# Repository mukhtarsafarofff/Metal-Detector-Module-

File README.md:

(ENG) We can find a metal detector at airports, theaters and various other public places. They are used for the safety of people to detect anyone carrying a metal.  In this project I am  going to design a simple metal detector circuit. There are so many metal detector designs but most of them are complex in design so here I am going to design a simple metal detector circuit using 555 Timer IC. In this circuit if the inductance value changes the value of reactance or impedance changes. The 555 IC timer here acts as a square wave generator and it generate pulses with frequencies audible to human. The capacitor between pin2 and pin1 should not be changed as it is need to generate audible frequencies. In this circuit you can see RLC circuit. RLC circuit is the metal detection part here. When a metal piece is brought near the coil, the metal piece acts as a core for the air cored inductor. By this metal acting as a core, the inductance of the coil changes or increases considerably. With this sudden increase in inductance of coil the overall reactance or impedance of the RLC circuit changes by a considerable amount when compared without the metal piece. At first when there is no metal piece the signal fed to speaker causes some audible sound. Now with the reactance change around the RLC circuit the signal sent to speaker will no longer be the same as before, because of this the sound produced by the speaker will be of different to the first one.  So whenever a metal is brought near the coil, the impedance of RLC changes making the signal to change resulting in variation to sound generated in speaker.  Enamel should be removed at the tips of coil for soldering connections. With different gauge we will have different RLC impedance, so one should experiment with resistance in RLC circuit for sensitive metal detection.

(DEU) Wir können Metalldetektoren an Flughäfen, in Theatern und an verschiedenen anderen öffentlichen Orten finden. Sie werden zur Sicherheit der Menschen eingesetzt, um Personen mit Metallgegenständen zu erkennen. In diesem Projekt werde ich einen einfachen Metalldetektorschaltkreis entwerfen. . Es gibt viele Metalldetektordesigns, aber die meisten sind komplex im Aufbau, daher werde ich hier einen einfachen Metalldetektorschaltkreis unter Verwendung eines 555-Timer-ICs entwerfen. In diesem Schaltkreis ändert sich der Wert der Reaktanz oder Impedanz, wenn sich der Induktivitätswert ändert.  Der 555-Timer-IC fungiert hier als Rechteckwellengenerator und erzeugt Impulse mit für den Menschen hörbaren Frequenzen. Der Kondensator zwischen Pin 2 und Pin 1 sollte nicht geändert werden, da er benötigt wird, um hörbare Frequenzen zu erzeugen.  In diesem Schaltkreis können Sie einen RLC-Schaltkreis sehen. Der RLC-Schaltkreis ist hier der Metalldetektionsteil. Wenn ein Metallstück in die Nähe der Spule gebracht wird, fungiert das Metallstück als Kern für die luftgekoppelte Induktivität. Durch dieses Metall, das als Kern fungiert, ändert oder erhöht sich die Induktivität der Spule erheblich.  Durch diese plötzliche Erhöhung der Induktivität der Spule ändert sich die gesamte Reaktanz oder Impedanz des RLC-Schaltkreises erheblich im Vergleich zu einem Zustand ohne Metallstück. Zunächst verursacht das Signal, das zum Lautsprecher geleitet wird, ein hörbares Geräusch, wenn kein Metallstück vorhanden ist.  Mit der Reaktanzänderung im RLC-Schaltkreis wird das Signal, das zum Lautsprecher gesendet wird, nicht mehr dasselbe sein wie zuvor, wodurch das vom Lautsprecher erzeugte Geräusch anders ist als das erste. Immer wenn ein Metall in die Nähe der Spule gebracht wird, ändert sich die Impedanz des RLC-Schaltkreises, wodurch sich das Signal ändert und somit das im Lautsprecher erzeugte Geräusch variiert.  Der Emaillelack sollte an den Enden der Spule für Lötverbindungen entfernt werden. Mit unterschiedlichem Drahtdurchmesser haben wir unterschiedliche RLC-Impedanzen, daher sollte man mit dem Widerstand im RLC-Schaltkreis experimentieren, um eine empfindliche Metalldetektion zu erreichen.

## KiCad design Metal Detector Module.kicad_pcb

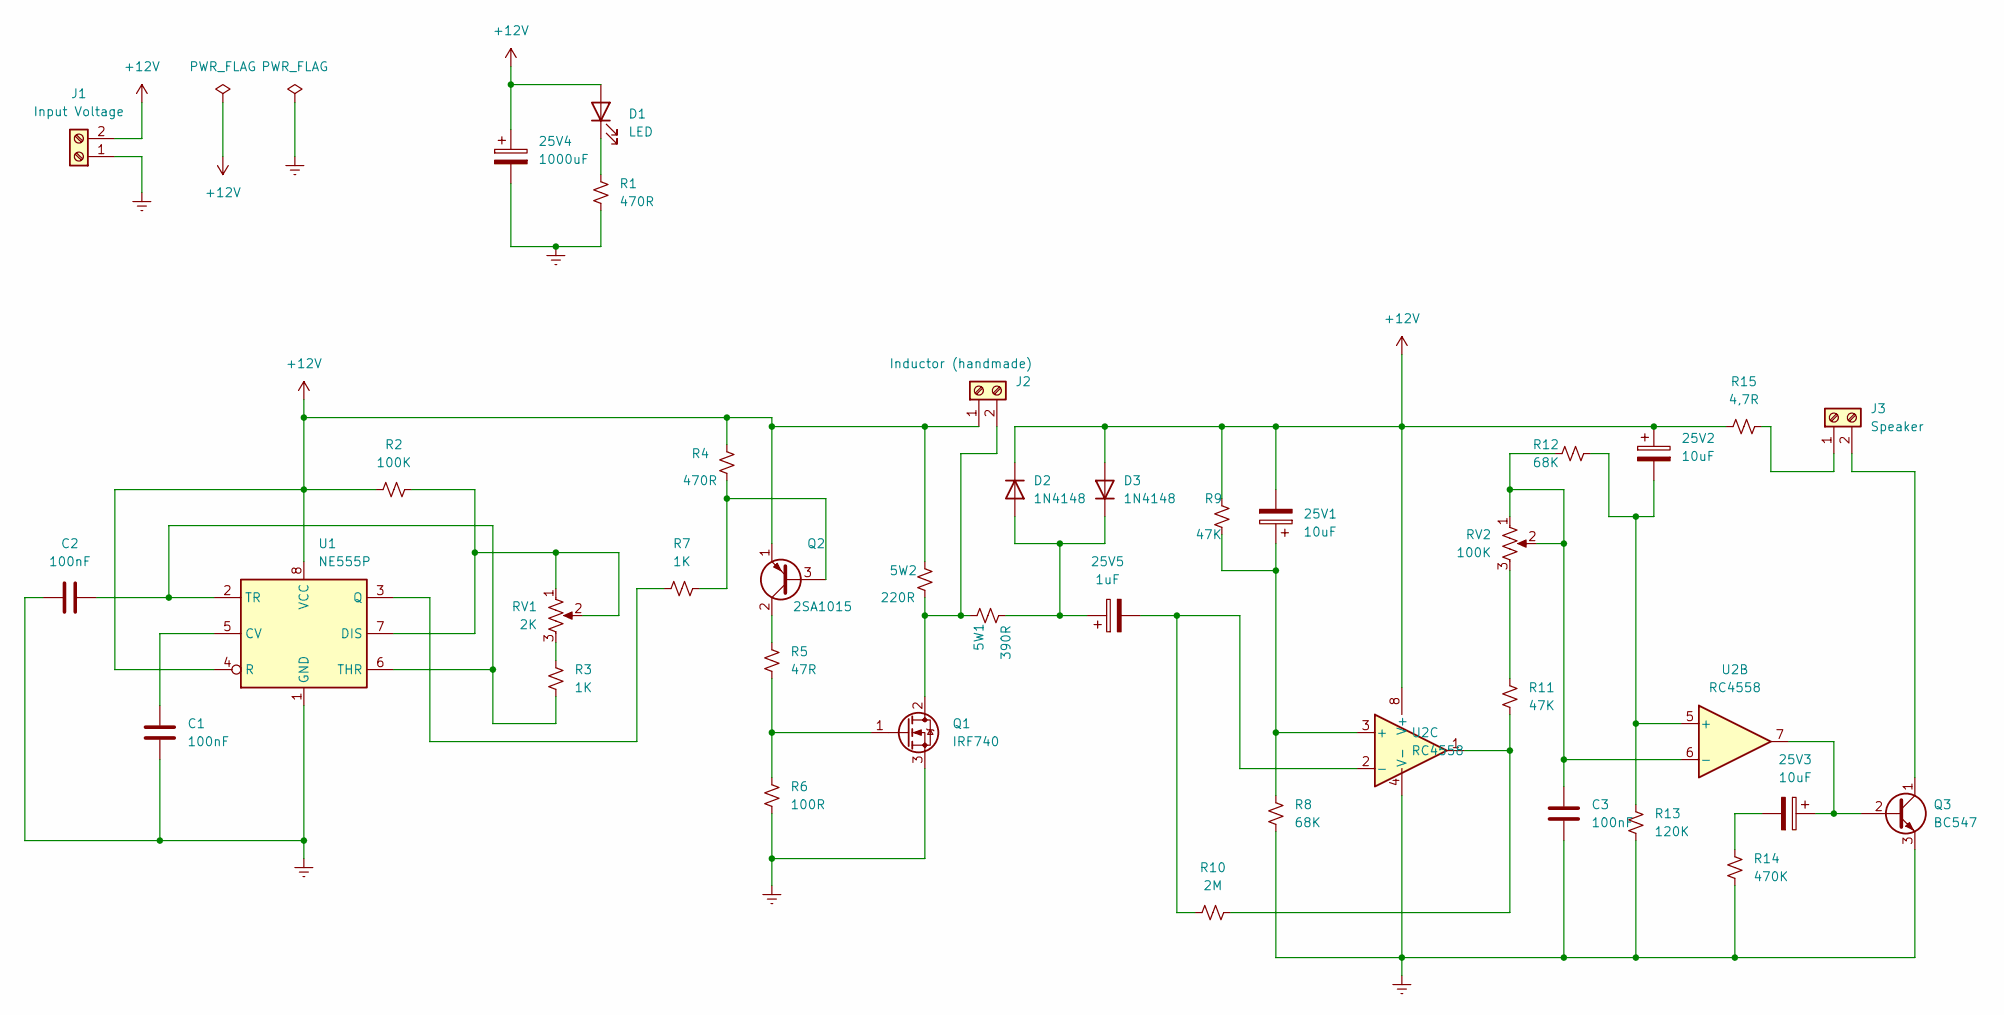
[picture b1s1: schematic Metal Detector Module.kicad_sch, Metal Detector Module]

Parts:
5W1: 390R; R_Axial_Power_L20.0mm_W6.4mm_P25.40mm
5W2: 220R; R_Axial_Power_L20.0mm_W6.4mm_P25.40mm
25V1, 25V2, 25V3: 10uF; CP_Radial_D16.0mm_P7.50mm
25V4: 1000uF; CP_Radial_D10.0mm_P7.50mm
25V5: 1uF; CP_Radial_D10.0mm_P7.50mm
C1, C2, C3: 100nF; C_Disc_D7.5mm_W5.0mm_P7.50mm
D1: LED; LED_D5.0mm
D2, D3: 1N4148; D_DO-35_SOD27_P7.62mm_Horizontal
J1: Input Voltage; TerminalBlock_bornier-2_P5.08mm
J2: Inductor (handmade); TerminalBlock_bornier-2_P5.08mm
J3: Speaker; TerminalBlock_bornier-2_P5.08mm
Q1: IRF740; TO-220-3_Vertical
Q2: 2SA1015; TO-92_Inline
Q3: BC547; TO-92_Inline
R1, R4: 470R; R_Axial_DIN0207_L6.3mm_D2.5mm_P15.24mm_Horizontal
R2: 100K; R_Axial_DIN0207_L6.3mm_D2.5mm_P15.24mm_Horizontal
R3, R7: 1K; R_Axial_DIN0207_L6.3mm_D2.5mm_P15.24mm_Horizontal
R5: 47R; R_Axial_DIN0207_L6.3mm_D2.5mm_P15.24mm_Horizontal
R6: 100R; R_Axial_DIN0207_L6.3mm_D2.5mm_P15.24mm_Horizontal
R8, R12: 68K; R_Axial_DIN0207_L6.3mm_D2.5mm_P15.24mm_Horizontal
R9, R11: 47K; R_Axial_DIN0207_L6.3mm_D2.5mm_P15.24mm_Horizontal
R10: 2M; R_Axial_DIN0207_L6.3mm_D2.5mm_P15.24mm_Horizontal
R13: 120K; R_Axial_DIN0207_L6.3mm_D2.5mm_P15.24mm_Horizontal
R14: 470K; R_Axial_DIN0207_L6.3mm_D2.5mm_P15.24mm_Horizontal
R15: 4,7R; R_Axial_DIN0207_L6.3mm_D2.5mm_P15.24mm_Horizontal
RV1: 2K; Potentiometer_Vishay_148-149_Single_Horizontal
RV2: 100K; Potentiometer_Vishay_148-149_Single_Horizontal
U1: NE555P; DIP-8_W7.62mm
U2: RC4558; DIP-8_W7.62mm

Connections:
+12V: 5W2.2, 25V1.2, 25V2.1, 25V4.1, D1.2 (A), D2.1 (K), D3.2 (A), J1.2, J2.1, Q2.1 (E), R2.1, R4.2, R9.2, R15.2, U1.4 (R), U1.8 (VCC), U2.8 (V+)
Earth: 25V4.2, C1.2, C2.1, C3.1, J1.1, Q1.3 (S), Q3.3 (E), R1.1, R6.1, R8.1, R13.1, R14.1, U1.1 (GND), U2.4 (V-)
unnamed: 25V3.2, R14.2
unnamed: D1.1 (K), R1.2
unnamed: 5W1.1, 25V5.1, D2.2 (A), D3.1 (K)
unnamed: 5W1.2, 5W2.1, J2.2, Q1.2 (D)
unnamed: J3.1, R15.1
unnamed: J3.2, Q3.1 (C)
unnamed: Q1.1 (G), R5.1, R6.2
unnamed: Q2.3 (B), R4.1, R7.2
unnamed: Q2.2 (C), R5.2
unnamed: 25V3.1, Q3.2 (B), U2.7
unnamed: R3.1, RV1.3
unnamed: R10.1, R11.1, U2.1
unnamed: R11.2, RV2.3
unnamed: C1.1, U1.5 (CV)
unnamed: R2.2, RV1.1, RV1.2, U1.7 (DIS)
unnamed: R7.1, U1.3 (Q)
unnamed: C2.2, R3.2, U1.2 (TR), U1.6 (THR)
unnamed: 25V1.1, R8.2, R9.1, U2.3 (+)
unnamed: 25V5.2, R10.2, U2.2 (-)
unnamed: 25V2.2, R12.1, R13.2, U2.5 (+)
unnamed: C3.2, R12.2, RV2.1, RV2.2, U2.6 (-)

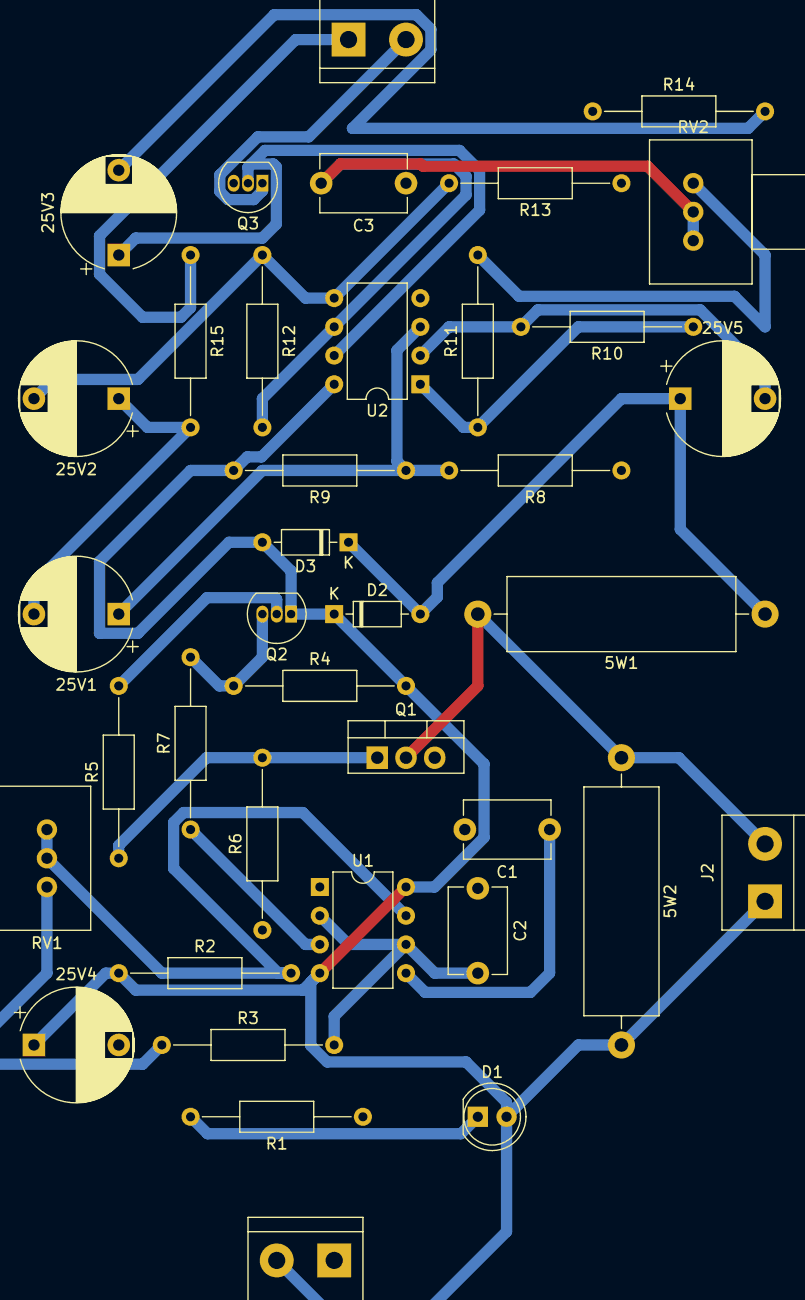
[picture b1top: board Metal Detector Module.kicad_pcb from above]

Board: 2 copper layers, 38 parts (0 on the bottom side), 23 nets.

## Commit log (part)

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2024-03-21 Metal detector Module is accomplished
2024-03-24 Metal Detector Module is renewed
